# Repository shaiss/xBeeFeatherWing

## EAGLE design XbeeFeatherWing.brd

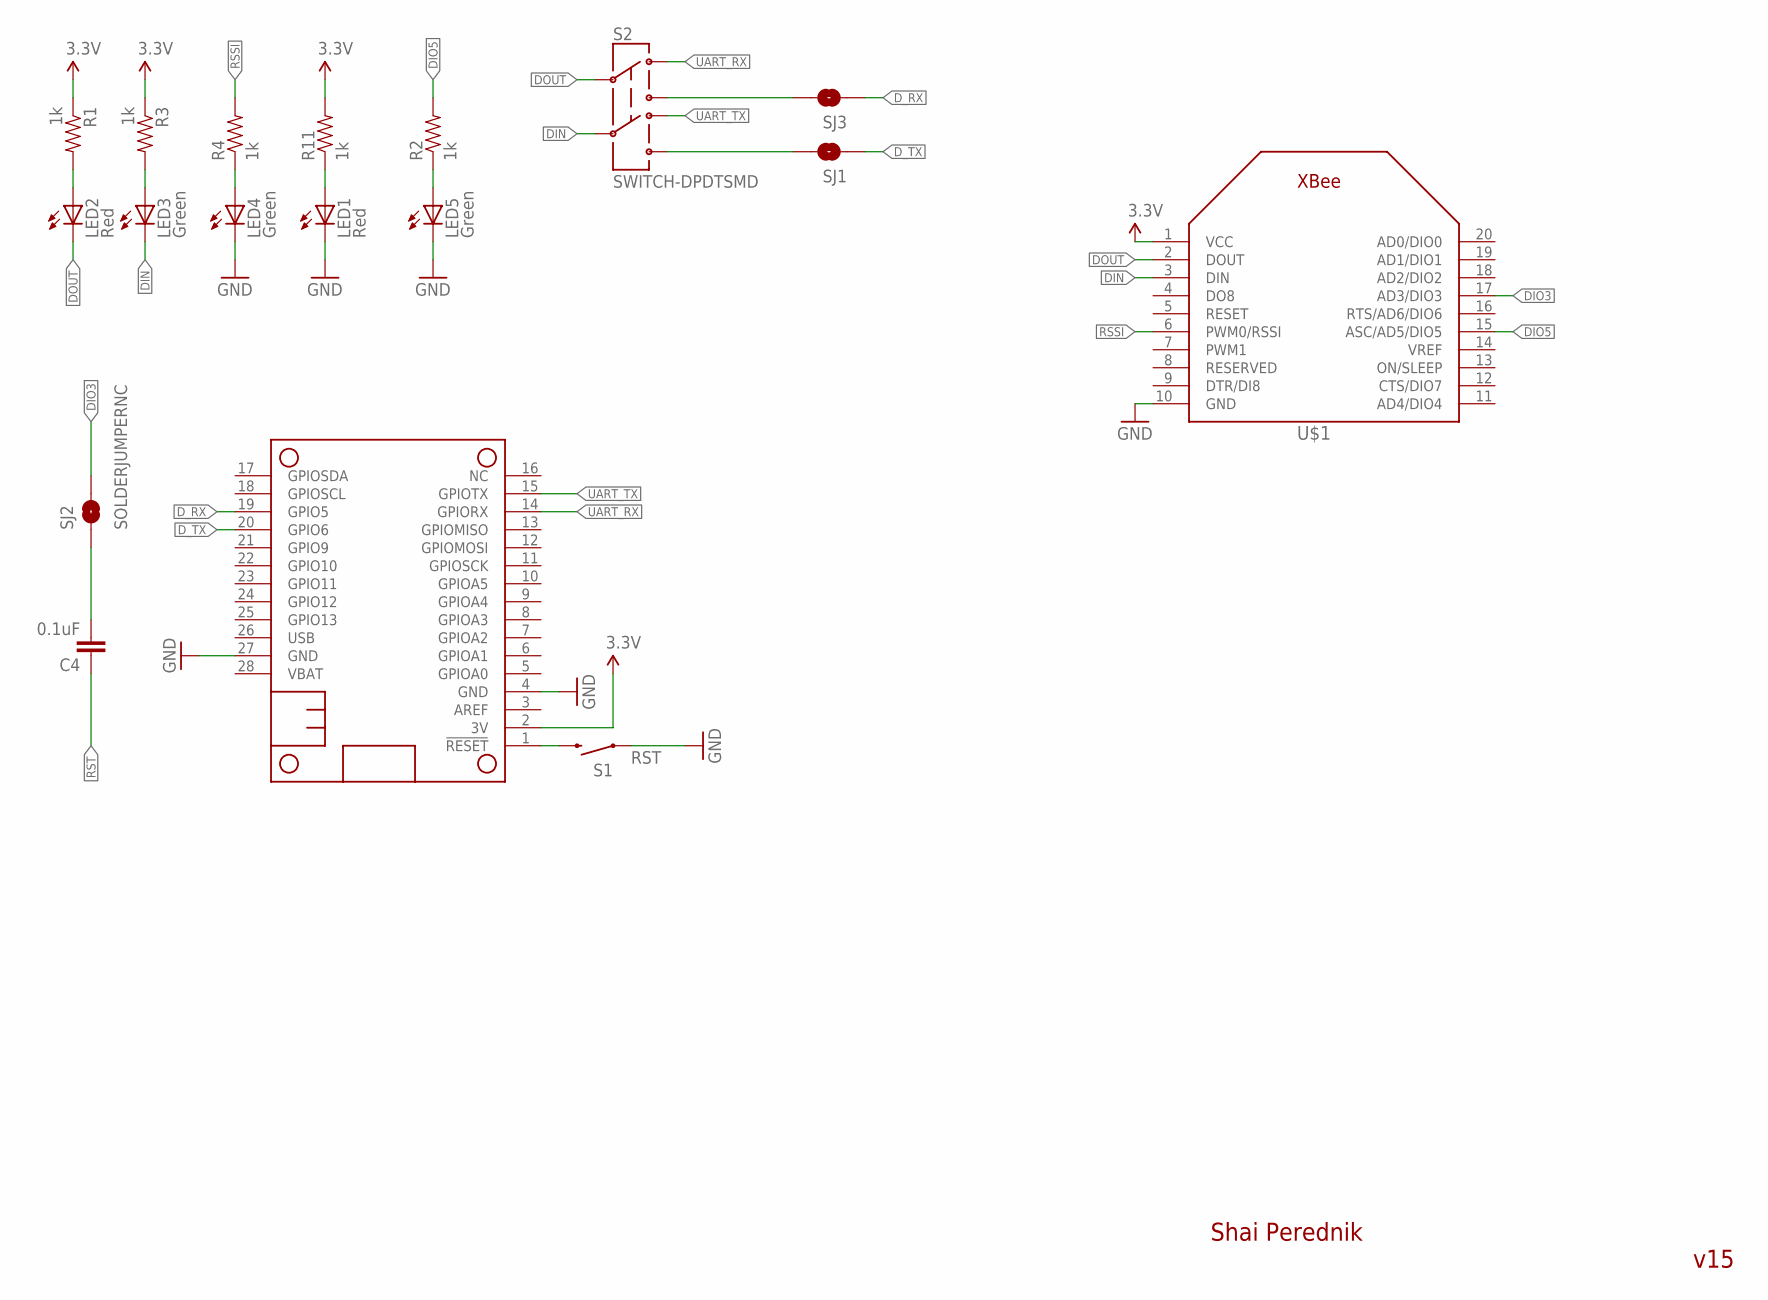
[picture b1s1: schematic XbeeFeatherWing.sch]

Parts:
C4: 0.1uF; 0603-CAP
LED1, LED2: Red; LED-0603
LED3, LED4, LED5: Green; LED-0603
MS2: MICROSHIELD_NODIM; MICROSHIELD_DIM
R1, R2, R3, R4, R11: 1k; 0603-RES
S1: SWITCH-MOMENTARY-2SMD; TACTILE_SWITCH_SMD
S2: SWITCH-DPDTSMD; AYZ0202
SJ1: D_TX; SJ_2S
SJ2: SOLDERJUMPERNC; SJ_2S
SJ3: D_RX; SJ_2S
U$1: XBEE

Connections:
3.3V: MS2.2 (3V), R1.1, R3.1, R11.2, U$1.1 (VCC)
DIN: LED3.C, S2.5, U$1.3 (DIN)
DIO3: SJ2.2, U$1.17 (AD3/DIO3)
DIO5: R2.2, U$1.15 (ASC/AD5/DIO5)
DOUT: LED2.C, S2.2, U$1.2 (DOUT)
D_RX: MS2.19 (GPIO5), SJ3.1
D_TX: MS2.20 (GPIO6), SJ1.1
GND: LED1.C, LED4.C, LED5.C, MS2.4 (GND), MS2.27 (GND), S1.1, U$1.10 (GND)
unnamed: LED2.A, R1.2
unnamed: LED4.A, R4.1
unnamed: LED3.A, R3.2
unnamed: C4.2, SJ2.1
unnamed: LED1.A, R11.1
unnamed: LED5.A, R2.1
unnamed: S2.6, SJ1.2
unnamed: S2.3, SJ3.2
RSSI: R4.2, U$1.6 (PWM0/RSSI)
RST: C4.1, MS2.1 (!RESET), S1.3 (2)
UART_RX: MS2.14 (GPIORX), S2.1
UART_TX: MS2.15 (GPIOTX), S2.4

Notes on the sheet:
Shai Perednik
v15

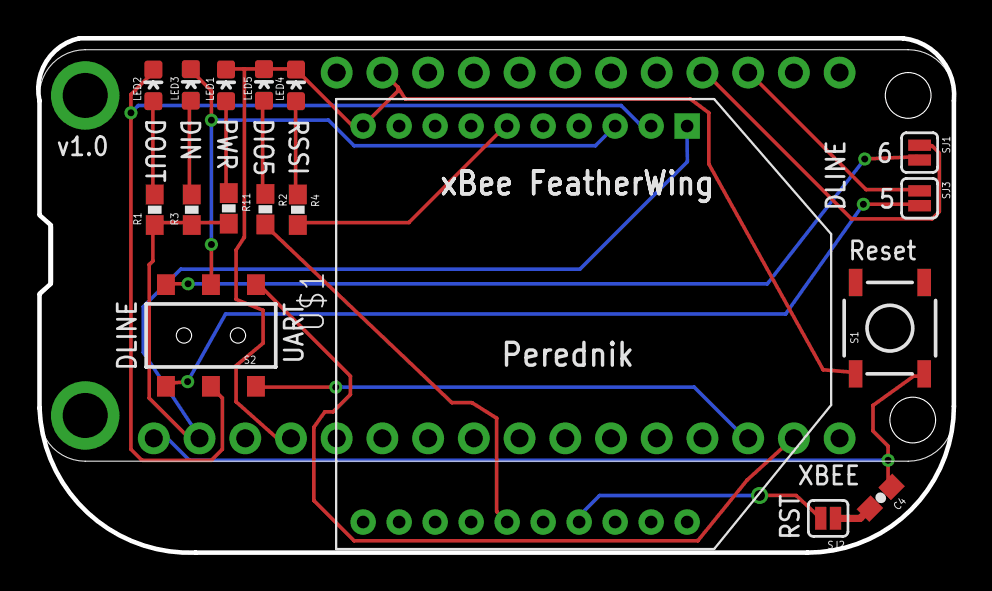
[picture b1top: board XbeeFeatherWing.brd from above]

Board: 2 copper layers, 50.9 x 28.6 mm, 18 parts (0 on the bottom side), 20 nets.

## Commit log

2016-02-10 :tada: Added .gitattributes & .gitignore files
2016-02-10 cleaned up pins
2016-02-10 changed xbee to adafruit footprint
    the sparkfun footprint was smd, needed THT pins
2016-02-23 v1 of the board with layout complete
2016-02-23 routing complete
2016-02-23 done routing & layout
    ready for fab

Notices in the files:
parts and their libraries:
SparkFun-Resistors: Licensing: Creative Commons ShareAlike 4.0 International - https://creativecommons.org/licenses/by-sa/4.0
